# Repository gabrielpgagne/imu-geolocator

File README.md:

# imu-geolocator
An experimental project about trying to use an IMU as a geolocalization device.

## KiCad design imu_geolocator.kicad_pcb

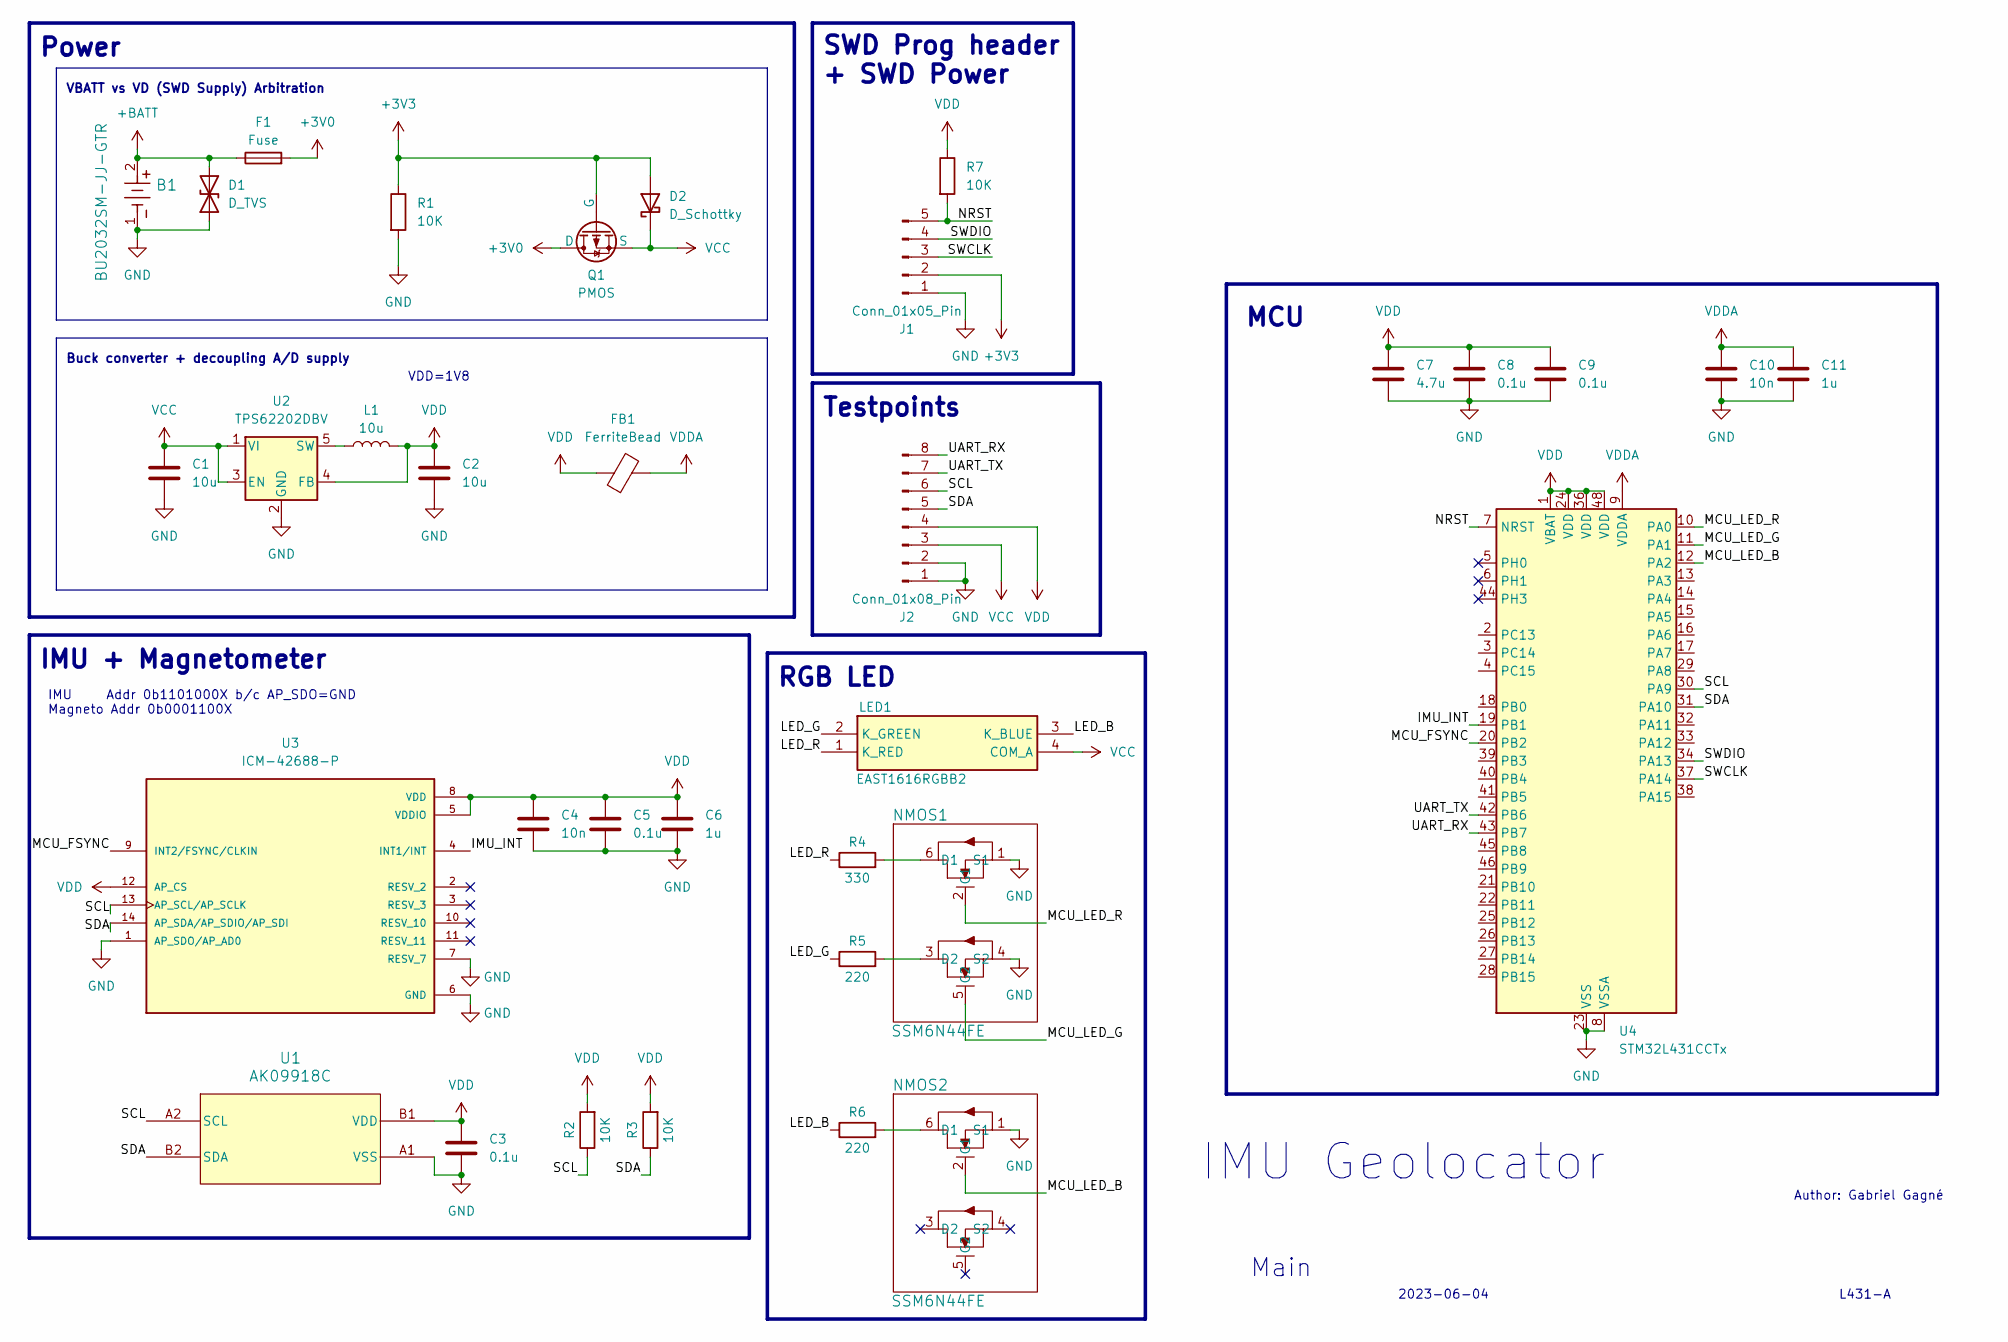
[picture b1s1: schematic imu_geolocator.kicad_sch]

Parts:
B1: BU2032SM-JJ-GTR; BU2032SM-JJ-GTR_MPD
C1, C2: 10u; C_0603_1608Metric
C3, C5, C8, C9: 0.1u; C_0603_1608Metric
C4, C10: 10n; C_0603_1608Metric
C6, C11: 1u; C_0603_1608Metric
C7: 4.7u; C_0603_1608Metric
D1: D_TVS; D_SOD-323F
D2: D_Schottky; D_SOD-123F
F1: Fuse; Fuse_0603_1608Metric
FB1: FerriteBead; L_0603_1608Metric
J1: Conn_01x05_Pin; PinHeader_1x05_P2.54mm_Vertical
J2: Conn_01x08_Pin; PinHeader_1x08_P2.54mm_Vertical
L1: 10u; L_Changjiang_FNR6028S
LED1: EAST1616RGBB2
NMOS1, NMOS2: SSM6N44FE; ES6
Q1: PMOS; SOT-723
R1, R2, R3, R7: 10K; R_0603_1608Metric
R4: 330; R_0603_1608Metric
R5, R6: 220; R_0603_1608Metric
U1: AK09918C; BGA4_WL-CSP_AKM
U2: TPS62202DBV; SOT-23-5
U3: ICM-42688-P; PQFN50P300X250X97-14N
U4: STM32L431CCTx; LQFP-48_7x7mm_P0.5mm

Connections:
+3V0: F1.2, Q1.1 (D)
+3V3: D2.2 (A), J1.2, Q1.2 (G), R1.1
+BATT: B1.2, D1.2 (A2), F1.1
/IMU_INT: U3.4 (INT1/INT), U4.19 (PB1)
/LED_B: LED1.3 (K_BLUE), R6.1
/LED_G: LED1.2 (K_GREEN), R5.1
/LED_R: LED1.1 (K_RED), R4.1
/MCU_FSYNC: U3.9 (INT2/FSYNC/CLKIN), U4.20 (PB2)
/MCU_LED_B: NMOS2.2 (G1), U4.12 (PA2)
/MCU_LED_G: NMOS1.5 (G2), U4.11 (PA1)
/MCU_LED_R: NMOS1.2 (G1), U4.10 (PA0)
/NRST: J1.5, R7.2, U4.7 (NRST)
/SCL: J2.6, R2.1, U1.A2 (SCL), U3.13 (AP_SCL/AP_SCLK), U4.30 (PA9)
/SDA: J2.5, R3.1, U1.B2 (SDA), U3.14 (AP_SDA/AP_SDIO/AP_SDI), U4.31 (PA10)
/SWCLK: J1.3, U4.37 (PA14)
/SWDIO: J1.4, U4.34 (PA13)
/UART_RX: J2.8, U4.43 (PB7)
/UART_TX: J2.7, U4.42 (PB6)
GND: B1.1, C1.2, C2.2, C3.2, C4.2, C5.2, C6.2, C7.2, C8.2, C9.2, C10.2, C11.2, D1.1 (A1), J1.1, J2.1, J2.2, NMOS1.1 (S1), NMOS1.4 (S2), NMOS2.1 (S1), R1.2, U1.A1 (VSS), U2.2 (GND), U3.1 (AP_SDO/AP_AD0), U3.6 (GND), U3.7 (RESV_7), U4.8 (VSSA), U4.23 (VSS), U4.35 (VSS), U4.47 (VSS)
unnamed: NMOS1.6 (D1), R4.2
unnamed: NMOS1.3 (D2), R5.2
unnamed: NMOS2.6 (D1), R6.2
unnamed: L1.1, U2.5 (SW)
VCC: C1.1, D2.1 (K), J2.3, LED1.4 (COM_A), Q1.3 (S), U2.1 (VI), U2.3 (EN)
VDD: C2.1, C3.1, C4.1, C5.1, C6.1, C7.1, C8.1, C9.1, FB1.1, J2.4, L1.2, R2.2, R3.2, R7.1, U1.B1 (VDD), U2.4 (FB), U3.5 (VDDIO), U3.8 (VDD), U3.12 (AP_CS), U4.1 (VBAT), U4.24 (VDD), U4.36 (VDD), U4.48 (VDD)
VDDA: C10.1, C11.1, FB1.2, U4.9 (VDDA)

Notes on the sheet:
Testpoints
L431-A
RGB LED
IMU Geolocator
Power
Main
IMU Addr 0b1101000X b/c AP_SDO=GND Magneto Addr 0b0001100X
Author: Gabriel Gagné
MCU
Buck converter + decoupling A/D supply
2023-06-04
VBATT vs VD (SWD Supply) Arbitration
IMU + Magnetometer
VDD=1V8
SWD Prog header + SWD Power

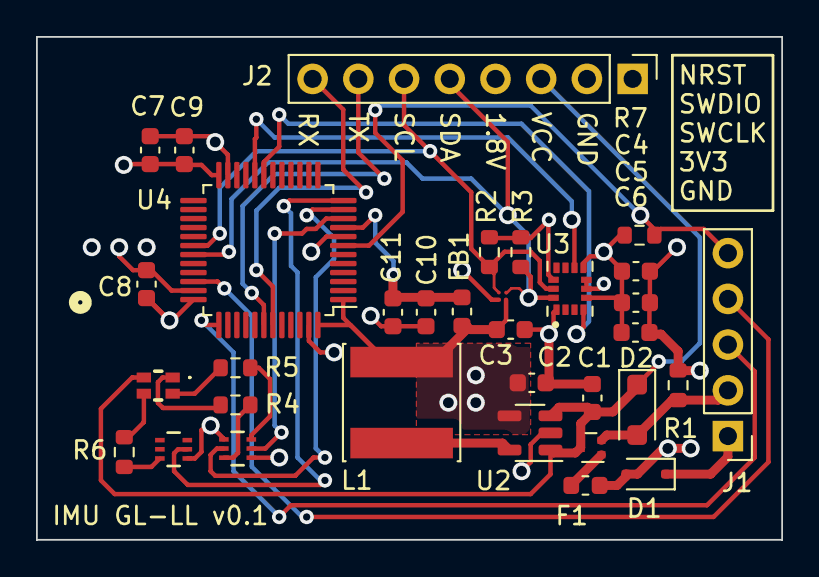
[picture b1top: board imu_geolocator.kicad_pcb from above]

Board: 4 copper layers, 41.4 x 27.9 mm, 34 parts (1 on the bottom side), 26 nets.

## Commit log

2023-06-04 First commit. Still need to figure out RF stuff.
2023-06-04 Create LICENSE
2023-06-04 Finished schematic v1, start PCB
2023-06-04 Routing in progress
2023-06-04 Finished routing v0.1
2023-06-04 Removed some useless silkscreen things
2023-06-04 Schematic done
2023-06-05 Routing done
2023-06-05 version 0.1-loraless finished
